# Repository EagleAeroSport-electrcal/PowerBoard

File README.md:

# PowerBoard

The structure might be a bit odd, because I'm using two additional libraries. One, which
was for the fuse symbol/footprint I made, was created locally within the project. The other,
the samacys stuff, for the converter and capacitor, was downloaded off mouser.

Additional note: I did edit the symbol for the converter, removing the leads for the mounting holes.
the hole/pads are still there in the footprint.

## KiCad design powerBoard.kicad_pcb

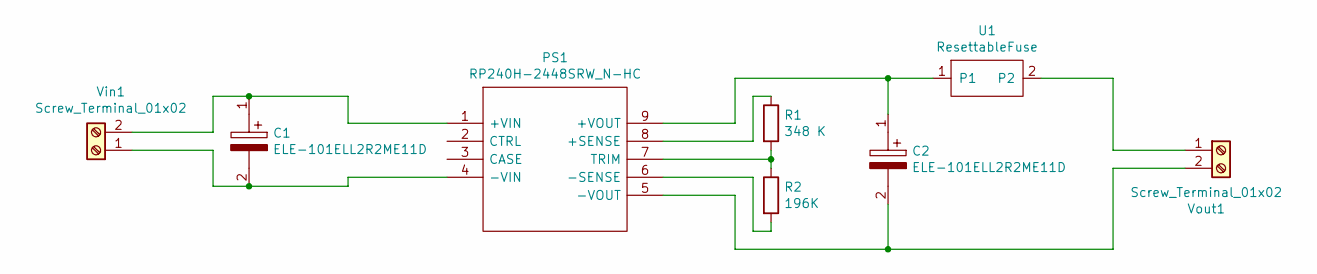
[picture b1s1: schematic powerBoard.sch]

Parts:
C1, C2: ELE-101ELL2R2ME11D; CAPPRD200W50D525H1250; Mouser Part Number 661-E-101L2R2ME11D
PS1: RP240H-2448SRW_N-HC; RP240H2448SRWNHC; Manufacturer_Part_Number RP240H-2448SRW/N-HC
R1: 348 K; R_Axial_DIN0614_L14.3mm_D5.7mm_P20.32mm_Horizontal
R2: 196K; R_Axial_DIN0614_L14.3mm_D5.7mm_P20.32mm_Horizontal
U1: ResettableFuse
Vin1: Screw_Terminal_01x02; TerminalBlock_bornier-2_P5.08mm
Vout1: Screw_Terminal_01x02; TerminalBlock_bornier-2_P5.08mm

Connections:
unnamed: C1.1, PS1.1 (+VIN), Vin1.2
unnamed: C1.2, PS1.4 (-VIN), Vin1.1
unnamed: C2.1, PS1.9 (+VOUT), U1.1
unnamed: C2.2, PS1.5 (-VOUT), Vout1.2
unnamed: PS1.6 (-SENSE), R2.2
unnamed: PS1.7 (TRIM), R1.2, R2.1
unnamed: PS1.8 (+SENSE), R1.1
unnamed: U1.2, Vout1.1

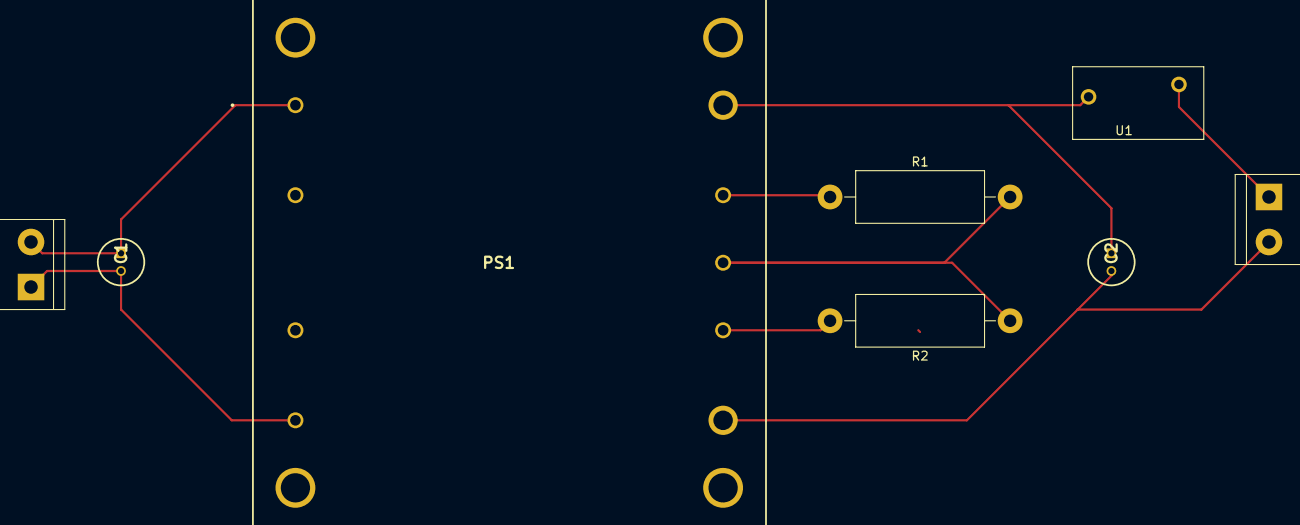
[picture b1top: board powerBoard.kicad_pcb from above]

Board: 2 copper layers, 8 parts (0 on the bottom side), 8 nets.

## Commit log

2021-09-28 Pushing updates from laptop
